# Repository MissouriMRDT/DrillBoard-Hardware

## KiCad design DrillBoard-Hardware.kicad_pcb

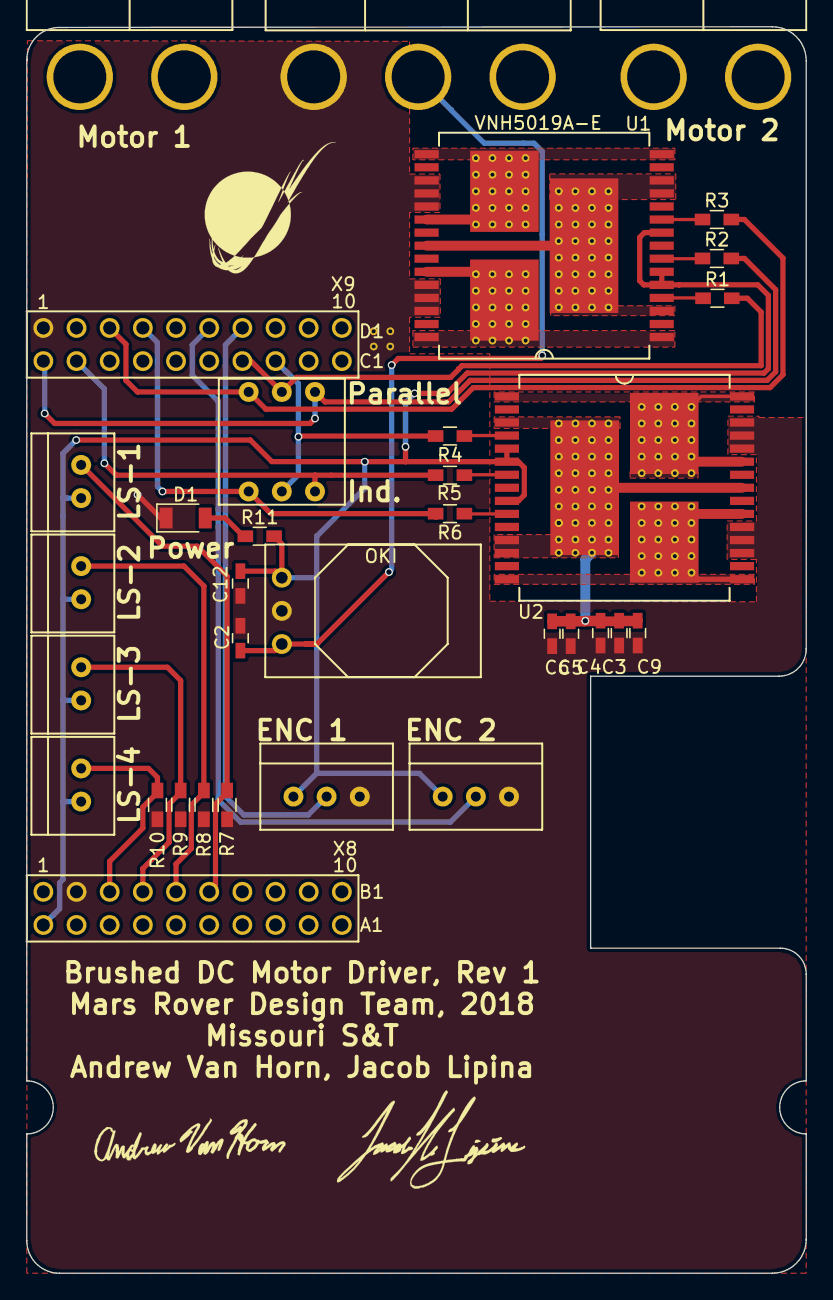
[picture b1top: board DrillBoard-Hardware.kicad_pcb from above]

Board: 2 copper layers, 59.7 x 95.5 mm, 33 parts (0 on the bottom side), 27 nets.

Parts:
C1: Anderson_3; Anderson_3_Horisontal_Side_by_Side
C2, C3, C5, C6, C9, C12: 10u; C_0603_HandSoldering
C4: .1u; C_0603_HandSoldering
C7, C8: Anderson-2; Anderson_2_Horisontal_Side_by_Side
D1: LED; D_1206
R1, R2, R3, R4, R5, R6: 1K; R_0603_HandSoldering
R7, R8, R9, R10: 10K; R_0603_HandSoldering
R11: 330; R_0603_HandSoldering
SW1: 3P1T_Fused; 3P1T_Switch
U1, U2: VNH5019A-E; MultiPowerSO_30
U3: OKI; OKI_Horisontal
U4: LS_1; MOLEX_SL_2_Vertical
U5: LS_2; MOLEX_SL_2_Vertical
U6: TM4C129E_Launchpad_X9
U7, U8: Picoblade-3; MOLEX_SL_3_Vertical
U9: LS_3; MOLEX_SL_2_Vertical
U10: LS_4; MOLEX_SL_2_Vertical

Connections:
+3V3: C12.1, R11.2, U1.5, U1.6, U1.9, U2.5, U2.6, U2.9, U3.3, U4.1, U5.1, U6.+3V3, U7.1, U8.1, U9.1, U10.1
+12V: C1.1, C3.1, C4.1, C5.1, C6.1, C9.1, U1.3, U1.12, U1.13, U1.23, U1.32, U2.3, U2.12, U2.13, U2.23, U2.32
/12V_Logic: C1.2, C2.1, U3.1
/Out_A1: C7.1, U1.1, U1.25, U1.30, U1.31
/Out_A2: C8.1, U2.1, U2.25, U2.30, U2.31
/Out_B1: C7.2, U1.15, U1.16, U1.21, U1.33
/Out_B2: C8.2, U2.15, U2.16, U2.21, U2.33
Encoder1_PWM: U6.PD0, U7.2
Encoder2_PWM: U6.PD1, U8.2
GND: C1.3, C2.2, C3.2, C4.2, C5.2, C6.2, C9.2, C12.2, D1.1, R7.2, R8.2, R9.2, R10.2, U1.18, U1.19, U1.20, U1.26, U1.27, U1.28, U2.18, U2.19, U2.20, U2.26, U2.27, U2.28, U3.2, U6.GND, U7.3, U8.3
IN_A1: R1.2, SW1.3, U6.PL0
IN_A2: R4.2, SW1.4, U6.PL1
IN_B1: R3.2, SW1.1, U6.PH2
IN_B2: R6.2, SW1.2, U6.PH3
LS_1: R7.1, U4.2, U6.PE3
LS_2: R8.1, U5.2, U6.PE2
LS_3: R9.1, U6.PE1, U9.2
LS_4: R10.1, U6.PE0, U10.2
unnamed: D1.2, R11.1
unnamed: R1.1, U1.4
unnamed: R2.1, U1.7
unnamed: R3.1, U1.10
unnamed: R4.1, U2.4
unnamed: R5.1, U2.7
unnamed: R6.1, U2.10
PWM1: R2.2, SW1.5, U6.PF1
PWM2: R5.2, SW1.6, U6.PF2

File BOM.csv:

Column1,Column2,Column3,Column4,Column5,Column6,Column7,Column8
Id,Designator,Package,Quantity,Designation,Supplier and ref,,
1,"REF**,REF**,REF**,REF**,REF**,REF**,REF**,REF**,REF**,REF**,REF**,REF**,REF**,REF**,REF**,REF**,REF**,REF**,REF**,REF**,REF**,REF**,REF**,REF**,REF**,REF**,REF**,REF**,REF**,REF**,REF**,REF**,REF**,REF**,REF**,REF**,REF**,REF**,REF**,REF**,REF**,REF**,REF**,REF**,REF**,REF**,REF**,REF**,REF**,REF**,REF**,REF**,REF**,REF**,REF**,REF**,REF**,REF**,REF**,REF**,REF**,REF**,REF**,REF**,REF**,REF**,REF**,REF**,REF**,REF**,REF**,REF**,REF**,REF**,REF**,REF**,REF**,REF**,REF**,REF**,REF**,REF**,REF**,REF**,REF**,REF**,REF**,REF**,REF**,REF**,REF**,REF**,REF**,REF**,REF**,REF**,REF**,REF**,REF**,REF**,REF**,REF**,REF**,REF**,REF**,REF**,REF**,REF**,REF**,REF**,REF**,REF**,REF**,REF**,REF**,REF**,REF**,REF**,REF**,REF**,REF**,REF**,REF**,REF**,REF**,REF**,REF**,REF**,REF**,REF**,REF**,REF**,REF**,REF**,REF**,REF**,REF**,REF**,REF**,REF**,REF**,REF**,REF**,REF**,REF**,REF**,REF**,REF**,REF**,REF**,REF**,REF**,REF**",Via_.6m,153,Via_P1.27mm_5x5,,,
2,U6,TM4C129E_Launchpad_X9,1,TM4C129E_Launchpad_X9,,,
3,"U8,U7",MOLEX_SL_3_Vertical,2,Picoblade-3,,,
4,U3,OKI_Horisontal,1,OKI,,,
5,U5,MOLEX_SL_2_Vertical,1,LS_2,,,
6,G***,Atlas_Logo_28.6mmX37.3mm,1,LOGO,,,
7,C4,C_0603_HandSoldering,1,.1u,,,
8,"U1,U2",MultiPowerSO_30,2,VNH5019A-E,,,
9,C1,Anderson_3_Horisontal_Side_by_Side,1,Anderson_3,,,
10,"C7,C8",Anderson_2_Horisontal_Side_by_Side,2,Anderson-2,,,
11,"R1,R2,R3,R4,R5,R6",R_0603_HandSoldering,6,1K,,,
12,SW1,3P1T_Switch,1,3P1T_Fused,,,
13,"C2,C12,C3,C5,C6,C9",C_0603_HandSoldering,6,10u,,,
14,G***,MRDT_Logo_10mm,1,LOGO,,,
15,G***,Andrew_Van_Horn_Sig_15mm,1,LOGO,,,
16,"R7,R8,R9,R10",R_0603_HandSoldering,4,10K,,,
17,U4,MOLEX_SL_2_Vertical,1,LS_1,,,
18,U9,MOLEX_SL_2_Vertical,1,LS_3,,,
19,U10,MOLEX_SL_2_Vertical,1,LS_4,,,
20,G***,Jacob_Lipina_Sig_15mm,1,LOGO,,,
21,D1,D_1206,1,LED,,,
22,R11,R_0603_HandSoldering,1,330,,,

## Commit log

2018-03-05 Started the Drill board project
2018-03-11 Developed schmatic
2018-03-14 General layout done, routing is a work in progress.
2018-03-19 Created board layout
    Will run traces this wek in preparation for board review next Sunday.
2018-03-22 Finished Board
2018-03-25 Finalized schematic and board and generated Gerbs
2018-03-26 Added Power LED and Gerbs
2018-03-28 Generated Final Gerbs
2018-04-16 Modified Gerbers
2018-04-22 Created New Gerbs
2018-04-22 Created New Gerb
2018-05-04 Added BOM

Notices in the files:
parts and their libraries:
Copyright 2016 Accelerated Designs. All rights reserved.
